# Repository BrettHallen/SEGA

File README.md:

# Sega Projects
The Sega Saturn was my first console (apart from my dad's Atari 2600), so has a special place in memory.<br>

## Sega Mark III
### [RGB amplifier](/Mark_III)<br>
An internal & external RGB video signal amplifier.<br>

## Sega SC-3000
I did start working on a homebrew SC-3000 ... but an already, far-superior [version](https://github.com/barbeque/sg1000) based on the SG-1000 has already been created.  You just need to add an SK-1100 keyboard ... DIY version also under development.<br>

## Sega Saturn
### [Windows Communication Cable](/Saturn/Windows_Communication_Cable)<br>

### [Saturn Keyboard (HSS-0129)](/Saturn/Keyboard)<br>
Started work on a homebrew version of the Saturn's keyboard.

.jpg)

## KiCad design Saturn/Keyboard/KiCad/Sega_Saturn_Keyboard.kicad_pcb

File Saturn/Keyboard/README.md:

# Sega Saturn Keyboard (HSS-0129)
The Sega Saturn Keyboard is an 89 key keyboard released for the Sega Saturn console.  It connects via the standard 9-pin Saturn controller and allowed you to use the Internet (in combination with the modem & mouse), program in Saturn BASIC (in combination with the floppy disc drive) and play Typing Of The Dead.<br>

I thought it might be interesting to reproduce it.<br>

## Background Analysis
Some excellent analysis has been done already on the Saturn's controller protocol:
- [Saturn Controller Protocol MK80117 and Emulation](https://nfggames.com/forum2/index.php?topic=5055.0)
- [Saturn keyboard scan codes](https://plutiedev.com/saturn-keyboard#scancodes)
- [Evolution of Sega's controllers](https://hackaday.io/project/170365-blueretro/log/180790-evolution-of-segas-io-interface-from-sg-1000-to-saturn#)
- [USB controller to Saturn via Arduino](https://github.com/garybethel/DS4toSaturn)

## Keyboard Matrix
I dismantled my keyboard and figured out the keyboard matrix - it uses two thin film sheets to register key presses.<br>

The matrix has 14 rows and 8 columns (by my reckoning) and connects to a small controller board internally via a 23-way connector (CN2, pin 15 is not use).  The columns have a pull-up resistor so I assume the rows are scanned and the columns are read.<br>

|  |COLUMN 0|COLUMN 1|COLUMN 2|COLUMN 3|COLUMN 4|COLUMN 5|COLUMN 6|COLUMN 7|
|---|--------|--------|--------|--------|--------|--------|--------|--------|
|ROW 0||LH CTRL|||RH CTRL||||
|ROW 1|LH SHIFT|||||RH SHIFT|||
|ROW 2|PAUSE|SCROLL LOCK|PRINT SCREEN|F12|F11|F10|F9|F8|
|ROW 3|PAGE UP|PAGE DOWN|RIGHT|DOWN|LEFT|UP|_ \ |? /|
|ROW 4|END|Z|SPACE|前候補|カタカナ|無変換||> .|
|ROW 5|HOME|X|ENTER|} ]|* :|+ ;|L|K|
|ROW 6|INSERT|A|DELETE|{ [|' @|P|O|I|
|ROW 7|BACKSPACE|S|\| ¥|_ ^|= -|- 0|) 9|( 8|
|ROW 8||C||V|B|N|M|< ,|
|ROW 9|CAPS LOCK|D|||F|G|H|J|
|ROW 10|半角/全角|E|TAB|W|RH CTRL|T|Y|U|
|ROW 11|! 1|Q|“ 2|# 3|$ 4|% 5|& 6|' 7|
|ROW 12|F1|ESC|F2|F3|F4|F5|F6|F7|
|ROW 13|||LH ALT|RH ALT|||||

## Controller
The keyboard has an internal controller board based around the Motorola MC68HC05C4 microcontroller.  This 8-bit MCU has about 4KB of internal ROM. <br>

The controller board connects to the Saturn via its 9-pin controller port which uses a 4-bit protocol to communicate.  Interestingly the internal pinout this connector (CN1) doesn't match the controller's pinout.  Weird.  The signals are all pulled up.<br>

| Controller | CN1 | Notes            | Direction        |
|------------|-----|------------------|------------------|
| 1          | 9   | +5V power        | Saturn->Keyboard |
| 2          | 3   | Data 1 (D)       | Keyboard->Saturn |
| 3          | 4   | Data 0 (U)       | Keyboard->Saturn |
| 4          | 5   | SELect (S0, TH)  | Saturn->Keyboard |
| 5          | 8   | REQuest (S1, TR) | Saturn->Keyboard |
| 6          | 7   | ACKnowledge (TL) | Keyboard->Saturn |
| 7          | 1   | Data 3 (R)       | Keyboard->Saturn |
| 8          | 2   | Data 2 (L)       | Keyboard->Saturn |
| 9          | 6   | GND              | Keyboard->Saturn |

### Further notes
- The REQ/TR signal acts as the serial clock
- The SEL/TH signal acts as a chip enable
- The ACK/TL signal indicates data is available on the bus
- The DATA0/U signal is high when idle, whereas DATA1 to DATA3 are low

## Keys
This Japanese keyboard has some additional keys with Kanji labels.  Here's a quick, rough translation - they are all related to entry of Japanese or Roman characters.<br>

| Japanese | English |
|----------|---------|
| 半角/全角 | Half-width/Full-width |
| 英数 | Alphanumeric |
| 漢字番号 | Kanji Number |
| 無変換 | No Conversion |
| 前候補 | Previous Candidate |
| 無変換(次候補) | No Conversion (Next Cadidate) |
| 全候補 | All Candidates |
| 漢字 | Kanji |
| カタカナ | Katakana |
| ひらがな | Hiragana |
| ローマ字 | Roman Characters |

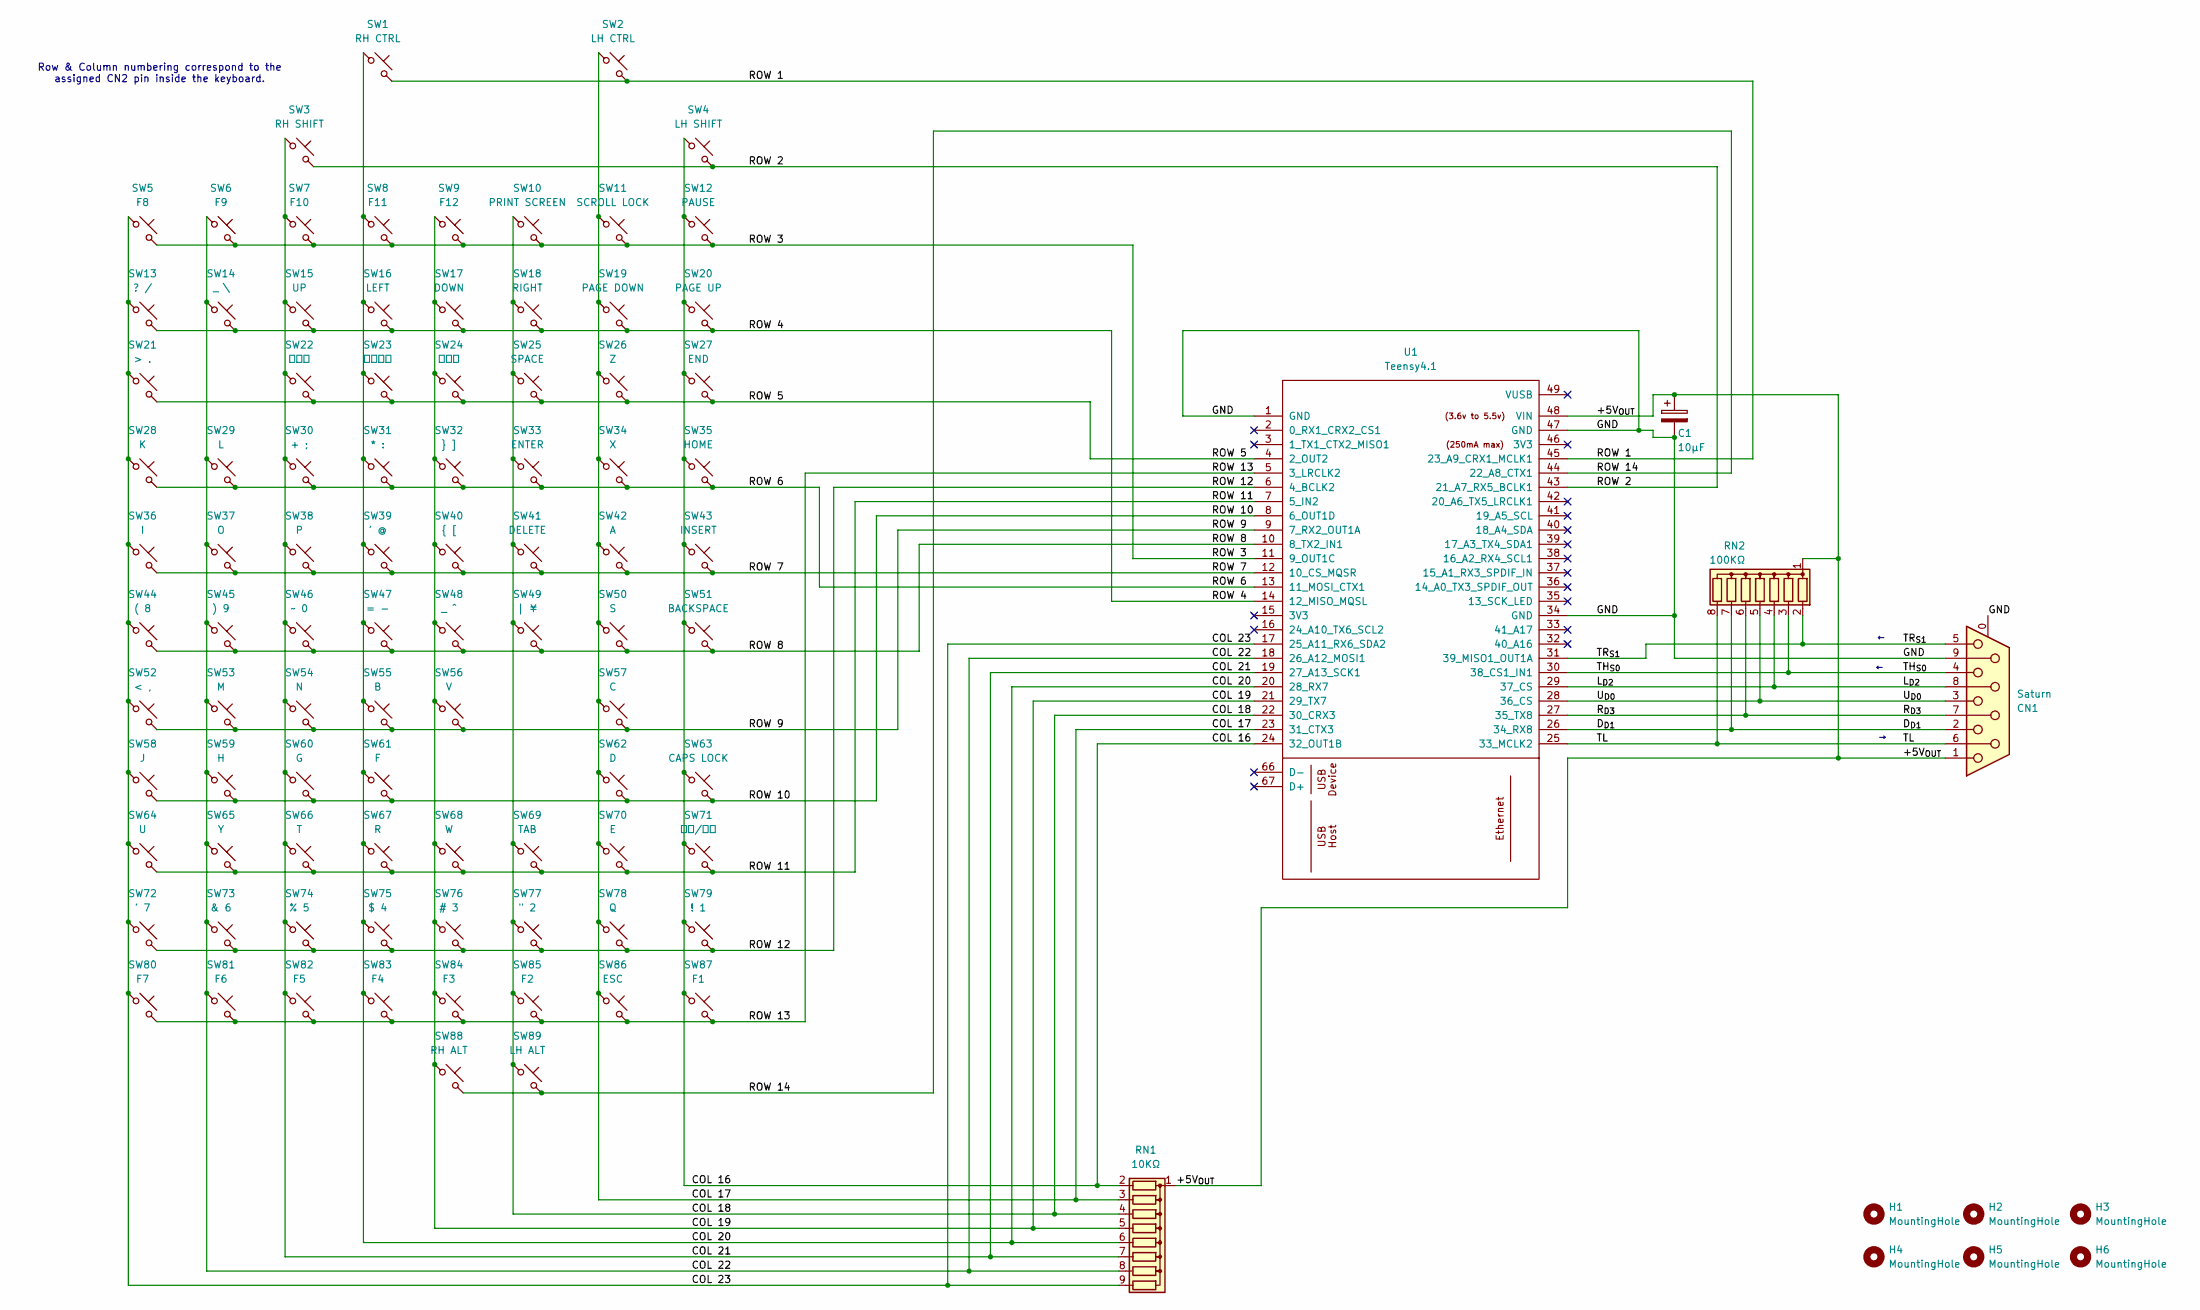
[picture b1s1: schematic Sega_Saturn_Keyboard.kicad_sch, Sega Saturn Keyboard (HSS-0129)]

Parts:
C1: 10µF; CP_Radial_D8.0mm_P2.50mm
CN1: Saturn; DSUB-9_Socket_Horizontal_P2.77x2.84mm_EdgePinOffset7.70mm_H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
H1, H2, H3, H4, H5, H6: MountingHole; MountingHole_3.2mm_M3
RN1: 10KΩ; R_Array_SIP9
RN2: 100KΩ; R_Array_SIP8
SW1: RH CTRL; SW_Cherry_MX_PCB_1.75u
SW2: LH CTRL; SW_Cherry_MX_PCB_1.50u
SW3: RH SHIFT; SW_Cherry_MX_PCB_2.00u
SW4: LH SHIFT; SW_Cherry_MX_PCB_2.00u
SW5: F8; SW_Cherry_MX_PCB_1.00u
SW6: F9; SW_Cherry_MX_PCB_1.00u
SW7: F10; SW_Cherry_MX_PCB_1.00u
SW8: F11; SW_Cherry_MX_PCB_1.00u
SW9: F12; SW_Cherry_MX_PCB_1.00u
SW10: PRINT SCREEN; SW_Cherry_MX_PCB_1.00u
SW11: SCROLL LOCK; SW_Cherry_MX_PCB_1.00u
SW12: PAUSE; SW_Cherry_MX_PCB_1.00u
SW13: ? /; SW_Cherry_MX_PCB_1.00u
SW14: _ \; SW_Cherry_MX_PCB_1.00u
SW15: UP; SW_Cherry_MX_PCB_1.00u
SW16: LEFT; SW_Cherry_MX_PCB_1.00u
SW17: DOWN; SW_Cherry_MX_PCB_1.00u
SW18: RIGHT; SW_Cherry_MX_PCB_1.00u
SW19: PAGE DOWN; SW_Cherry_MX_PCB_1.00u
SW20: PAGE UP; SW_Cherry_MX_PCB_1.00u
SW21: > .; SW_Cherry_MX_PCB_1.00u
SW22: 無変換; SW_Cherry_MX_PCB_1.50u
SW23: カタカナ; SW_Cherry_MX_PCB_1.50u
SW24: 前候補; SW_Cherry_MX_PCB_1.50u
SW25: SPACE; SW_Cherry_MX_PCB_2.25u
SW26: Z; SW_Cherry_MX_PCB_1.00u
SW27: END; SW_Cherry_MX_PCB_1.00u
SW28: K; SW_Cherry_MX_PCB_1.00u
SW29: L; SW_Cherry_MX_PCB_1.00u
SW30: + ;; SW_Cherry_MX_PCB_1.00u
SW31: * :; SW_Cherry_MX_PCB_1.00u
SW32: } ]; SW_Cherry_MX_PCB_1.00u
SW33: ENTER; SW_Cherry_MX_PCB_ISOEnter
SW34: X; SW_Cherry_MX_PCB_1.00u
SW35: HOME; SW_Cherry_MX_PCB_1.00u
SW36: I; SW_Cherry_MX_PCB_1.00u
SW37: O; SW_Cherry_MX_PCB_1.00u
SW38: P; SW_Cherry_MX_PCB_1.00u
SW39: ' @; SW_Cherry_MX_PCB_1.00u
SW40: { [; SW_Cherry_MX_PCB_1.00u
SW41: DELETE; SW_Cherry_MX_PCB_1.00u
SW42: A; SW_Cherry_MX_PCB_1.00u
SW43: INSERT; SW_Cherry_MX_PCB_1.00u
SW44: ( 8; SW_Cherry_MX_PCB_1.00u
SW45: ) 9; SW_Cherry_MX_PCB_1.00u
SW46: ~ 0; SW_Cherry_MX_PCB_1.00u
SW47: = -; SW_Cherry_MX_PCB_1.00u
SW48: _ ^; SW_Cherry_MX_PCB_1.00u
SW49: | ¥; SW_Cherry_MX_PCB_1.00u
SW50: S; SW_Cherry_MX_PCB_1.00u
SW51: BACKSPACE; SW_Cherry_MX_PCB_1.00u
SW52: < ,; SW_Cherry_MX_PCB_1.00u
SW53: M; SW_Cherry_MX_PCB_1.00u
SW54: N; SW_Cherry_MX_PCB_1.00u
SW55: B; SW_Cherry_MX_PCB_1.00u
SW56: V; SW_Cherry_MX_PCB_1.00u
SW57: C; SW_Cherry_MX_PCB_1.00u
SW58: J; SW_Cherry_MX_PCB_1.00u
SW59: H; SW_Cherry_MX_PCB_1.00u
SW60: G; SW_Cherry_MX_PCB_1.00u
SW61: F; SW_Cherry_MX_PCB_1.00u
SW62: D; SW_Cherry_MX_PCB_1.00u
SW63: CAPS LOCK; SW_Cherry_MX_PCB_1.75u
SW64: U; SW_Cherry_MX_PCB_1.00u
SW65: Y; SW_Cherry_MX_PCB_1.00u
SW66: T; SW_Cherry_MX_PCB_1.00u
SW67: R; SW_Cherry_MX_PCB_1.00u
SW68: W; SW_Cherry_MX_PCB_1.00u
SW69: TAB; SW_Cherry_MX_PCB_1.50u
SW70: E; SW_Cherry_MX_PCB_1.00u
SW71: 半角/全角; SW_Cherry_MX_PCB_1.00u
SW72: ' 7; SW_Cherry_MX_PCB_1.00u
SW73: & 6; SW_Cherry_MX_PCB_1.00u
SW74: % 5; SW_Cherry_MX_PCB_1.00u
SW75: $ 4; SW_Cherry_MX_PCB_1.00u
SW76: # 3; SW_Cherry_MX_PCB_1.00u
SW77: " 2; SW_Cherry_MX_PCB_1.00u
SW78: Q; SW_Cherry_MX_PCB_1.00u
SW79: ! 1; SW_Cherry_MX_PCB_1.00u
SW80: F7; SW_Cherry_MX_PCB_1.00u
SW81: F6; SW_Cherry_MX_PCB_1.00u
SW82: F5; SW_Cherry_MX_PCB_1.00u
SW83: F4; SW_Cherry_MX_PCB_1.00u
SW84: F3; SW_Cherry_MX_PCB_1.00u
SW85: F2; SW_Cherry_MX_PCB_1.00u
SW86: ESC; SW_Cherry_MX_PCB_1.00u
SW87: F1; SW_Cherry_MX_PCB_1.00u
SW88: RH ALT; SW_Cherry_MX_PCB_1.50u
SW89: LH ALT; SW_Cherry_MX_PCB_1.50u
U1: Teensy4.1; Teensy41

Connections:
/+5V_{OUT}: C1.1, CN1.1, RN1.1 (common), RN2.1 (common), U1.48 (VIN)
/COL 16: RN1.2 (R1), SW4.1, SW12.1, SW20.1, SW27.1, SW35.1, SW43.1, SW51.1, SW63.1, SW71.1, SW79.1, SW87.1, U1.24 (32_OUT1B)
/COL 17: RN1.3 (R2), SW2.1, SW11.1, SW19.1, SW26.1, SW34.1, SW42.1, SW50.1, SW57.1, SW62.1, SW70.1, SW78.1, SW86.1, U1.23 (31_CTX3)
/COL 18: RN1.4 (R3), SW10.1, SW18.1, SW25.1, SW33.1, SW41.1, SW49.1, SW69.1, SW77.1, SW85.1, SW89.1, U1.22 (30_CRX3)
/COL 19: RN1.5 (R4), SW9.1, SW17.1, SW24.1, SW32.1, SW40.1, SW48.1, SW56.1, SW68.1, SW76.1, SW84.1, SW88.1, U1.21 (29_TX7)
/COL 20: RN1.6 (R5), SW1.1, SW8.1, SW16.1, SW23.1, SW31.1, SW39.1, SW47.1, SW55.1, SW61.1, SW67.1, SW75.1, SW83.1, U1.20 (28_RX7)
/COL 21: RN1.7 (R6), SW3.1, SW7.1, SW15.1, SW22.1, SW30.1, SW38.1, SW46.1, SW54.1, SW60.1, SW66.1, SW74.1, SW82.1, U1.19 (27_A13_SCK1)
/COL 22: RN1.8 (R7), SW6.1, SW14.1, SW29.1, SW37.1, SW45.1, SW53.1, SW59.1, SW65.1, SW73.1, SW81.1, U1.18 (26_A12_MOSI1)
/COL 23: RN1.9 (R8), SW5.1, SW13.1, SW21.1, SW28.1, SW36.1, SW44.1, SW52.1, SW58.1, SW64.1, SW72.1, SW80.1, U1.17 (25_A11_RX6_SDA2)
/D_{D1}: CN1.2, RN2.7 (R6), U1.26 (34_RX8)
/GND: C1.2, CN1.0 (PAD), CN1.9, U1.1 (GND), U1.34 (GND), U1.47 (GND)
/L_{D2}: CN1.8, RN2.4 (R3), U1.29 (37_CS)
/ROW 1: SW1.2, SW2.2, U1.45 (23_A9_CRX1_MCLK1)
/ROW 2: SW3.2, SW4.2, U1.43 (21_A7_RX5_BCLK1)
/ROW 3: SW5.2, SW6.2, SW7.2, SW8.2, SW9.2, SW10.2, SW11.2, SW12.2, U1.11 (9_OUT1C)
/ROW 4: SW13.2, SW14.2, SW15.2, SW16.2, SW17.2, SW18.2, SW19.2, SW20.2, U1.14 (12_MISO_MQSL)
/ROW 5: SW21.2, SW22.2, SW23.2, SW24.2, SW25.2, SW26.2, SW27.2, U1.4 (2_OUT2)
/ROW 6: SW28.2, SW29.2, SW30.2, SW31.2, SW32.2, SW33.2, SW34.2, SW35.2, U1.13 (11_MOSI_CTX1)
/ROW 7: SW36.2, SW37.2, SW38.2, SW39.2, SW40.2, SW41.2, SW42.2, SW43.2, U1.12 (10_CS_MQSR)
/ROW 8: SW44.2, SW45.2, SW46.2, SW47.2, SW48.2, SW49.2, SW50.2, SW51.2, U1.10 (8_TX2_IN1)
/ROW 9: SW52.2, SW53.2, SW54.2, SW55.2, SW56.2, SW57.2, U1.9 (7_RX2_OUT1A)
/ROW 10: SW58.2, SW59.2, SW60.2, SW61.2, SW62.2, SW63.2, U1.8 (6_OUT1D)
/ROW 11: SW64.2, SW65.2, SW66.2, SW67.2, SW68.2, SW69.2, SW70.2, SW71.2, U1.7 (5_IN2)
/ROW 12: SW72.2, SW73.2, SW74.2, SW75.2, SW76.2, SW77.2, SW78.2, SW79.2, U1.6 (4_BCLK2)
/ROW 13: SW80.2, SW81.2, SW82.2, SW83.2, SW84.2, SW85.2, SW86.2, SW87.2, U1.5 (3_LRCLK2)
/ROW 14: SW88.2, SW89.2, U1.44 (22_A8_CTX1)
/R_{D3}: CN1.7, RN2.6 (R5), U1.27 (35_TX8)
/TH_{S0}: CN1.4, RN2.3 (R2), U1.30 (38_CS1_IN1)
/TL: CN1.6, RN2.8 (R7), U1.25 (33_MCLK2)
/TR_{S1}: CN1.5, RN2.2 (R1), U1.31 (39_MISO1_OUT1A)
/U_{D0}: CN1.3, RN2.5 (R4), U1.28 (36_CS)

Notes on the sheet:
Row & Column numbering correspond to the assigned CN2 pin inside the keyboard.

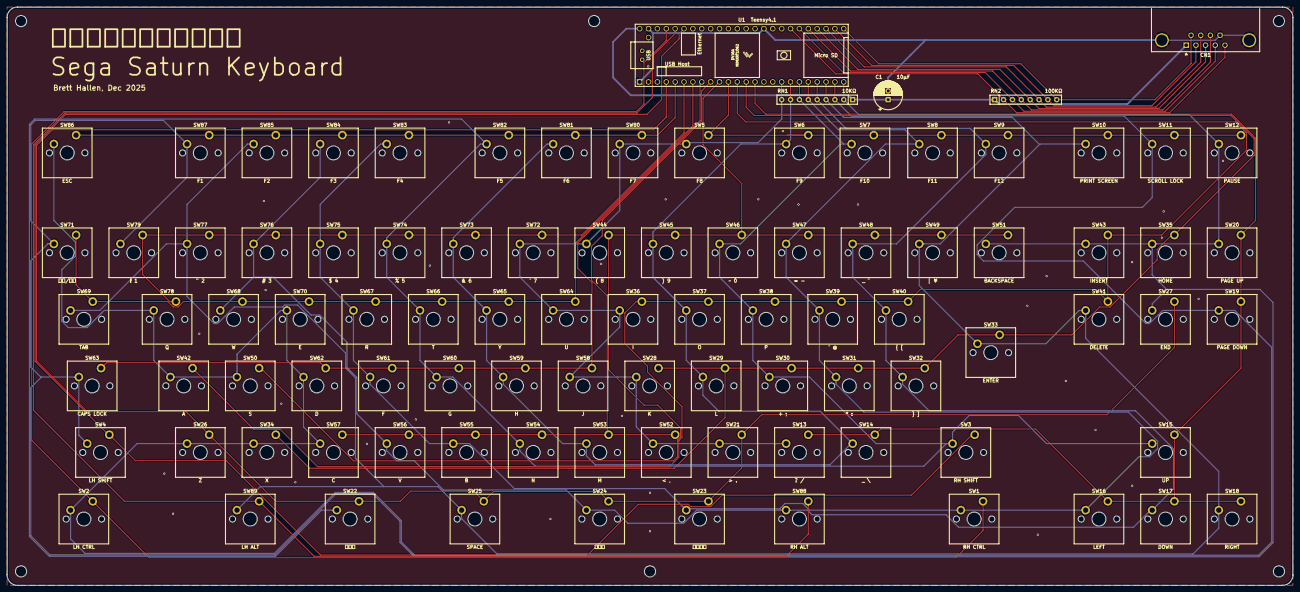
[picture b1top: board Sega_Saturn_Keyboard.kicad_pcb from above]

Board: 2 copper layers, 368.0 x 165.5 mm, 100 parts (0 on the bottom side), 31 nets.

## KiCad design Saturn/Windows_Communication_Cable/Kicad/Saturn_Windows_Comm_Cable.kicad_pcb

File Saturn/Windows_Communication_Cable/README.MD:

# Windows Communication Cable
# Windows通信ケーブル
This cable comes bundled with GAME BASIC for SEGA SATURN.<br>
The cable plugs into the Saturn's Communications port at one end and into a Window computer's RS232 serial port on the other end.<br>
It uses an [NEC D4711B](Documentation/NEC_UPD4711BGS_Datasheet.pdf) RS-232 line driver/receiver to handle the communications between the Saturn and the Windows machine.<br>

## Windows RS232
On the Windows side it uses two wires plus shield:<br>
- red (アカ) wire connected to pin 2 (RS232 Transmit)
- white (シロ) wire connected to pin 3 (RS232 Receive)
- shield (シールド) wire connected to pin 7 (RS232 signal ground) plus shield

The DE9 cable equivalents would be:<br>
- red (アカ) wire connected to pin 3 (RS232 Transmit)
- white (シロ) wire connected to pin 2 (RS232 Receive)
- shield (シールド) wire connected to pin 5 (RS232 signal ground) plus shield

## Sega Saturn Communication Port (looking at cable)
I don't know if this is the "official" pinout, but I read that the angled corner is supposed to indicate pin 11/12 and odd-on-top, even-on-bottom.  So this is what I've used.<br>
```
   11          1
 _________________
/  | | | | | | | |
|_|_|_|_|_|_|_|__|
 12           2
```
On the Saturn side it uses three wires plus shield:<br>
- red (アカ) to pin 2 (+5V power)
- white (シロ) to pin 5 (Saturn TTL to PC RS232)
- black (クロ) to pin 6 (PC RS232 to Saturn TTL)
- shield (シールド) to pins 8 & 12 (ground)

## Warning
The cable includes a warning:<br>
> 本製品を直接パソコンに接続しないでください。<br>
> パソコンとの接続の仕方はチュートリアルマニュアルをご覧下さい。

This translates as:<br>
> Do not connect this product directly to a computer.<br>
> Please see the tutorial manual for how to connect to a computer.

However the [manual](Documentation/Cable_Instructions_3_ENG.jpg) just details that an RS232 straight-through/modem cable should be used. My guess is that the cable is too short to properly connect the Saturn to your computer, so an extension cable should be used.<br>

The relevant three pages can be found in the [Documentation](Documentation) folder - both in original Japanese and Google-translated English.

## Sega Saturn to USB
How about connecting via USB?  You could use this original cable (or make one) and then use a USB-to-serial converter cable.<br>

But let's just drop the whole to/from RS232 conversion and go straight from TTL serial (Sega Saturn) to USB.  You can get cables that do this already, such as the [FTDI model TTL-232R-5V](https://ftdichip.com/products/ttl-232r-5v/).<br>

You still have the issue of connecting to the Saturn's obscure 12-pin serial port.  As you only need three pins (Rx, Tx and GND) you could make these available by adding your own port on the Saturn.<br>

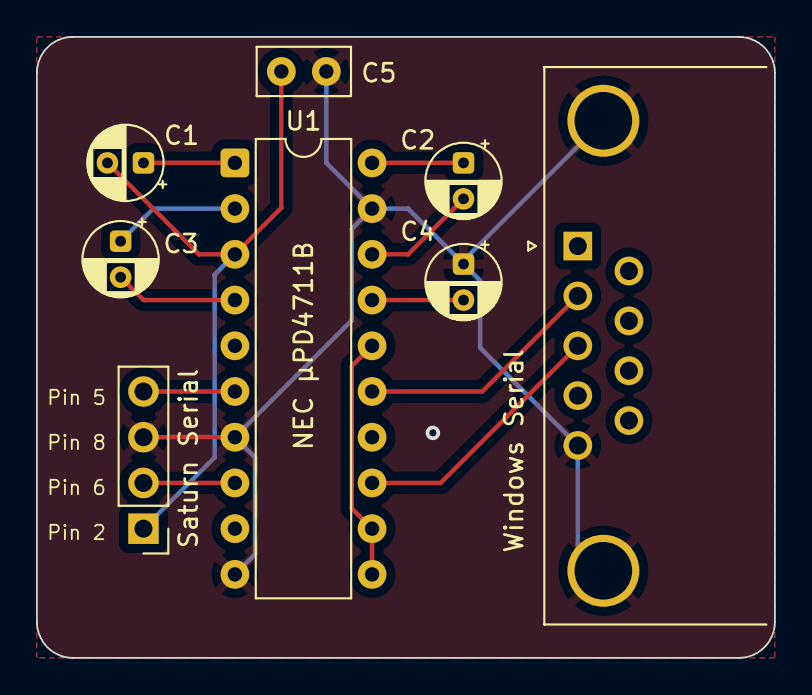
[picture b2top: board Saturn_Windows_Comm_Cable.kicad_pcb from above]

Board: 2 copper layers, 41.0 x 34.5 mm, 8 parts (0 on the bottom side), 13 nets.

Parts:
C1, C2, C3, C4: 1µF; CP_Radial_D4.0mm_P2.00mm
C5: 100nF; C_Disc_D5.0mm_W2.5mm_P2.50mm
J1: To Saturn Serial; PinHeader_1x04_P2.54mm_Vertical
J2: Windows Serial; DSUB-9_Socket_Horizontal_P2.77x2.84mm_EdgePinOffset7.70mm_H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
U1: NEC µPD4711B; DIP-20_W7.62mm

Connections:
/GND: C4.1, C5.2, J1.3, J2.0 (PAD), J2.5, U1.7 (D_{IN2}), U1.10 (GND), U1.19 (GND)
/SATURN_{アカ}: C1.2, C5.1, J1.1, U1.3 (V_{CC})
/SATURN_{クロ}: J1.2, U1.8 (R_{OUT1})
/SATURN_{シロ}: J1.4, U1.6 (D_{IN1})
/WIN_{RX}: J2.2, U1.15 (D_{OUT1})
/WIN_{TX}: J2.3, U1.13 (R_{IN1})
unnamed: C3.1, U1.2 (C_{1}^{+})
unnamed: C3.2, U1.4 (C_{1}^{-})
unnamed: C2.1, U1.20 (C_{4}^{+})
unnamed: C2.2, U1.18 (C_{4}^{-})
unnamed: U1.11 (R_{CON}), U1.12 (R_{IN2}), U1.16 (D_{CON})
unnamed: C1.1, U1.1 (V_{DD})
unnamed: C4.2, U1.17 (V_{SS})

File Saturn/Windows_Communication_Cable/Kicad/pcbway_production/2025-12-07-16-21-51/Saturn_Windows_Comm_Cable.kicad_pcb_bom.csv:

Designator,Quantity,Value,Footprint,Package,MPN,DNP,Mount_Type,Description
"C1, C2, C3, C4",4,1µF,CP_Radial_D4.0mm_P2.00mm,,,,tht,
C5,1,100nF,C_Disc_D5.0mm_W2.5mm_P2.50mm,,,,tht,
J1,1,To Saturn Serial,PinHeader_1x04_P2.54mm_Vertical,,,,tht,"Generic connector, single row, 01x04, script generated (kicad-library-utils/schlib/autogen/connector/)"
J2,1,Windows Serial,DSUB-9_Socket_Horizontal_P2.77x2.84mm_EdgePinOffset7.70mm_Housed_MountingHolesOffset9.12mm,,,,tht,"9-pin D-SUB connector, socket (female), Mounting Hole"
U1,1,NEC µPD4711B,DIP-20_W7.62mm,,,,tht,

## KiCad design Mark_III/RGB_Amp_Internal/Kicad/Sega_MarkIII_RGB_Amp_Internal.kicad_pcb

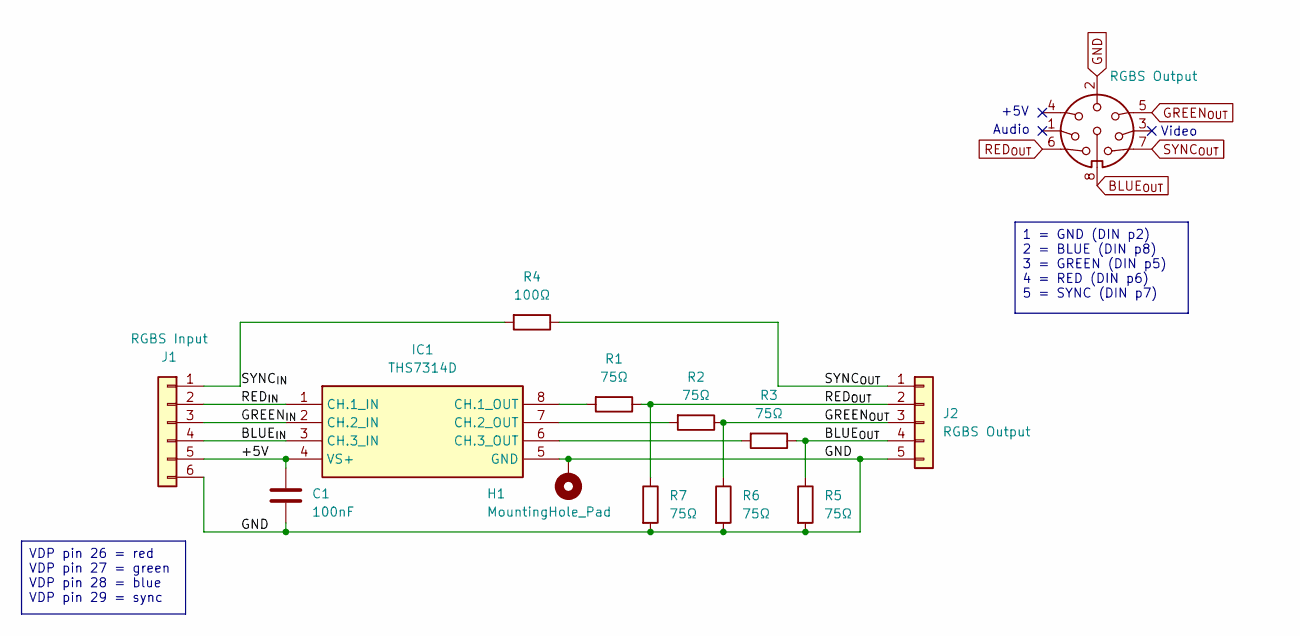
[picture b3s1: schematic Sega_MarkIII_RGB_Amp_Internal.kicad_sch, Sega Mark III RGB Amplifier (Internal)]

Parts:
C1: 100nF; C_0805_2012Metric_Pad1.18x1.45mm_HandSolder
H1: MountingHole_Pad; MountingHole_3.2mm_M3_DIN965_Pad_TopBottom
IC1: THS7314D; SOIC127P600X175-8N; Mouser Part Number 595-THS7314DR
J1: RGBS Input; PinHeader_1x06_P2.54mm_Horizontal
J2: RGBS Output; PinHeader_1x05_P2.54mm_Horizontal
J3: RGBS Output
R1, R2, R3, R5, R6, R7: 75Ω; R_0805_2012Metric_Pad1.20x1.40mm_HandSolder
R4: 100Ω; R_0805_2012Metric_Pad1.20x1.40mm_HandSolder

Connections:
/+5V: C1.2, IC1.4 (VS+), J1.5
/BLUE_{IN}: IC1.3 (CH.3_IN), J1.4
/GREEN_{IN}: IC1.2 (CH.2_IN), J1.3
/RED_{IN}: IC1.1 (CH.1_IN), J1.2
/SYNC_{IN}: J1.1, R4.2
BLUE_{OUT}: J2.4, R3.1, R5.1
GND: C1.1, H1.1, IC1.5 (GND), J1.6, J2.5, R5.2, R6.2, R7.2
GREEN_{OUT}: J2.3, R2.1, R6.1
unnamed: IC1.8 (CH.1_OUT), R1.2
unnamed: IC1.7 (CH.2_OUT), R2.2
unnamed: IC1.6 (CH.3_OUT), R3.2
RED_{OUT}: J2.2, R1.1, R7.1
SYNC_{OUT}: J2.1, R4.1

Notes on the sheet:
Audio
+5V
Video
VDP pin 26 = red VDP pin 27 = green VDP pin 28 = blue VDP pin 29 = sync
1 = GND (DIN p2) 2 = BLUE (DIN p8) 3 = GREEN (DIN p5) 4 = RED (DIN p6) 5 = SYNC (DIN p7)

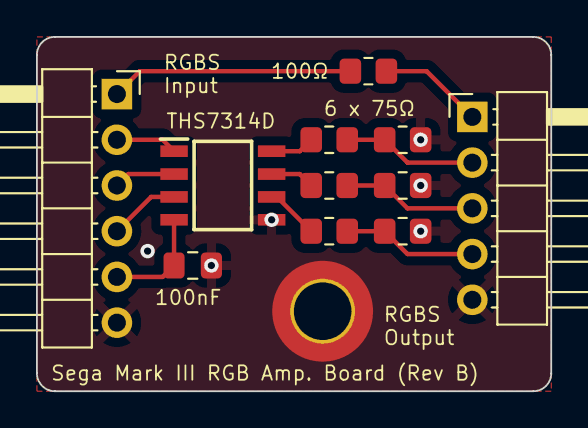
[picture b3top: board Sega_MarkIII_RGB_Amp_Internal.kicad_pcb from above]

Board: 2 copper layers, 28.6 x 19.7 mm, 12 parts (0 on the bottom side), 13 nets.

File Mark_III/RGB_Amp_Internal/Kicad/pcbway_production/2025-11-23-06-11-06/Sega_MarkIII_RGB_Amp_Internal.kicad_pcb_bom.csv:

Designator,Quantity,Value,Footprint,Package,MPN,DNP,Mount_Type,Height,Manufacturer_Name,Mouser Part Number,Mouser Price/Stock,Description
C1,1,100nF,C_0805_2012Metric_Pad1.18x1.45mm_HandSolder,,,,smt,,,,,
IC1,1,THS7314D,SOIC127P600X175-8N,,THS7314DR,,smt,1.75,Texas Instruments,595-THS7314DR,https://www.mouser.co.uk/ProductDetail/Texas-Instruments/THS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,
J1,1,RGBS Input,PinHeader_1x06_P2.54mm_Horizontal,,,,tht,,,,,"Generic connector, single row, 01x06, script generated (kicad-library-utils/schlib/autogen/connector/)"
J2,1,RGBS Output,PinHeader_1x05_P2.54mm_Horizontal,,,,tht,,,,,"Generic connector, single row, 01x05, script generated (kicad-library-utils/schlib/autogen/connector/)"
"R1, R2, R3, R5, R6, R7",6,75Ω,R_0805_2012Metric_Pad1.20x1.40mm_HandSolder,,,,smt,,,,,
R4,1,100Ω,R_0805_2012Metric_Pad1.20x1.40mm_HandSolder,,,,smt,,,,,

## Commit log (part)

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2025-12-02 Keyboard layout
2025-12-02 Redesigned PCB
2025-12-02 Added document with English translations for Kanji labels
2025-12-02 Analysed matrix & started PCB routing
2025-12-03 Initial PCB routing completed
2025-12-03 Added 100KΩ value for pull-up
2025-12-03 Additional text on PCB
2025-12-03 Added additional images
2025-12-07 Revised original SS schematic
2025-12-07 Reorganise folders
2025-12-07 Added info about Saturn-to-USB
2025-12-07 Swapped DE9 male -> female
2025-12-09 Example controller signalling
    Saleae Logic file
2025-12-09 Design tweaks
2026-01-21 Value text on PCB moved to F.Silkscreen
